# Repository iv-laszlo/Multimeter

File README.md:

# Multimeter

This project is a custom-built Digital Multimeter developed by a student team, as part of an academic project. The device is capable of measuring voltage, current, and resistance, and was designed from the ground up using embedded systems and custom PCB design.

Features

    Measures DC voltage, current, resistance, and temperature

    Built using a microcontroller with analog signal processing

    Designed in KiCad for schematic and PCB layout

    Fully functional firmware written in C/C++

    Simple and intuitive user interface

Tools & Technologies

    Microcontroller: Aruino Nano [ATmega328P]

    KiCad: PCB and schematic design

    C/C++: Firmware development

    Multimeter principles: Analog signal acquisition, ADC, display interface

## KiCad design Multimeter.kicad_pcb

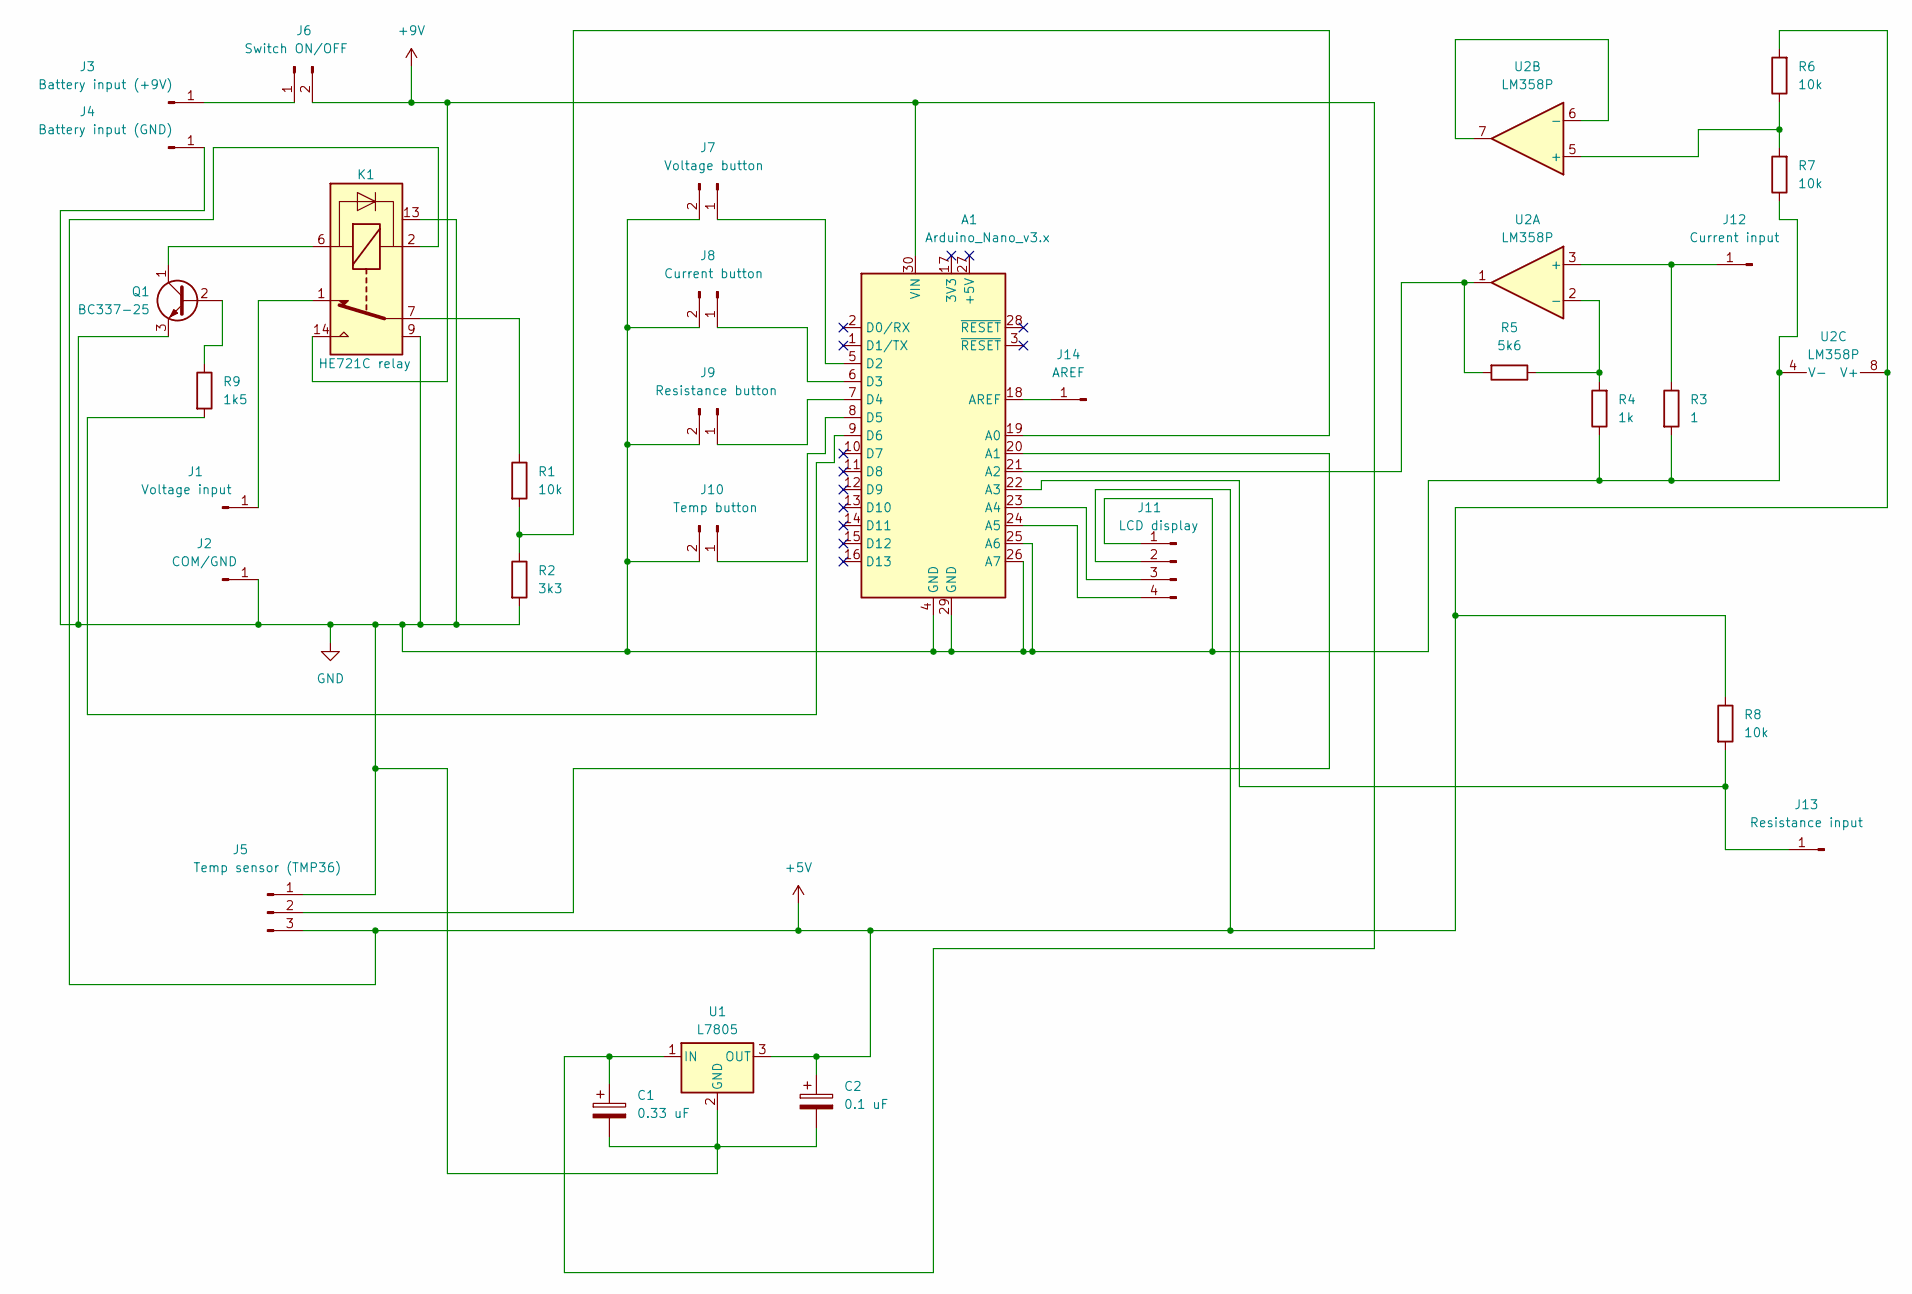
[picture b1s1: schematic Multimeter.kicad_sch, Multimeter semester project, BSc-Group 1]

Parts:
A1: Arduino_Nano_v3.x; Arduino_Nano
C1: 0.33 uF; CP_Radial_Tantal_D4.5mm_P2.50mm
C2: 0.1 uF; CP_Radial_Tantal_D4.5mm_P2.50mm
J1: Voltage input; PinHeader_1x01_P2.54mm_Vertical
J2: COM/GND; PinHeader_1x01_P2.54mm_Vertical
J3: Battery input (+9V); PinHeader_1x01_P2.54mm_Vertical
J4: Battery input (GND); PinHeader_1x01_P2.54mm_Vertical
J5: Temp sensor (TMP36); PinHeader_1x03_P2.54mm_Vertical
J6: Switch ON/OFF; PinHeader_1x02_P2.54mm_Vertical
J7: Voltage button; PinHeader_1x02_P2.54mm_Vertical
J8: Current button; PinHeader_1x02_P2.54mm_Vertical
J9: Resistance button; PinHeader_1x02_P2.54mm_Vertical
J10: Temp button; PinHeader_1x02_P2.54mm_Vertical
J11: LCD display; PinHeader_1x04_P2.54mm_Vertical
J12: Current input; PinHeader_1x01_P2.54mm_Vertical
J13: Resistance input; PinHeader_1x01_P2.54mm_Vertical
J14: AREF; PinHeader_1x01_P2.54mm_Vertical
K1: HE721C relay; HE700
Q1: BC337-25; TO-92_Inline_Wide
R1, R6, R7, R8: 10k; R_Axial_DIN0207_L6.3mm_D2.5mm_P10.16mm_Horizontal
R2: 3k3; R_Axial_DIN0207_L6.3mm_D2.5mm_P10.16mm_Horizontal
R3: 1; R_Axial_DIN0207_L6.3mm_D2.5mm_P10.16mm_Horizontal
R4: 1k; R_Axial_DIN0207_L6.3mm_D2.5mm_P10.16mm_Horizontal
R5: 5k6; R_Axial_DIN0207_L6.3mm_D2.5mm_P10.16mm_Horizontal
R9: 1k5; R_Axial_DIN0207_L6.3mm_D2.5mm_P10.16mm_Horizontal
U1: L7805; TO-220-3_Vertical
U2: LM358P; DIP-8_W7.62mm

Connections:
+5V: C2.1, J5.3, J11.2, K1.2, R6.2, R8.1, U1.3 (OUT), U2.8 (V+)
+9V: A1.30 (VIN), C1.1, J6.2, K1.14, U1.1 (IN)
GND: A1.4 (GND), A1.25 (A6), A1.26 (A7), A1.29 (GND), C1.2, C2.2, J2.1, J4.1, J5.1, J7.2, J8.2, J9.2, J10.2, J11.1, K1.9, K1.13, Q1.3 (E), R2.2, R3.2, R4.1, R7.1, U1.2 (GND), U2.4 (V-)
unnamed: A1.19 (A0), R1.2, R2.1
unnamed: A1.20 (A1), J5.2
unnamed: A1.21 (A2), R5.2, U2.1
unnamed: A1.22 (A3), J13.1, R8.2
unnamed: A1.23 (A4), J11.3
unnamed: A1.24 (A5), J11.4
unnamed: A1.18 (AREF), J14.1
unnamed: A1.5 (D2), J7.1
unnamed: A1.6 (D3), J8.1
unnamed: A1.7 (D4), J9.1
unnamed: A1.8 (D5), J10.1
unnamed: A1.9 (D6), R9.2
unnamed: J1.1, K1.1
unnamed: J3.1, J6.1
unnamed: J12.1, R3.1, U2.3 (+)
unnamed: K1.7, K1.8, R1.1
unnamed: Q1.2 (B), R9.1
unnamed: K1.6, Q1.1 (C)
unnamed: R4.2, R5.1, U2.2 (-)
unnamed: R6.1, R7.2, U2.5 (+)
unnamed: U2.6 (-), U2.7

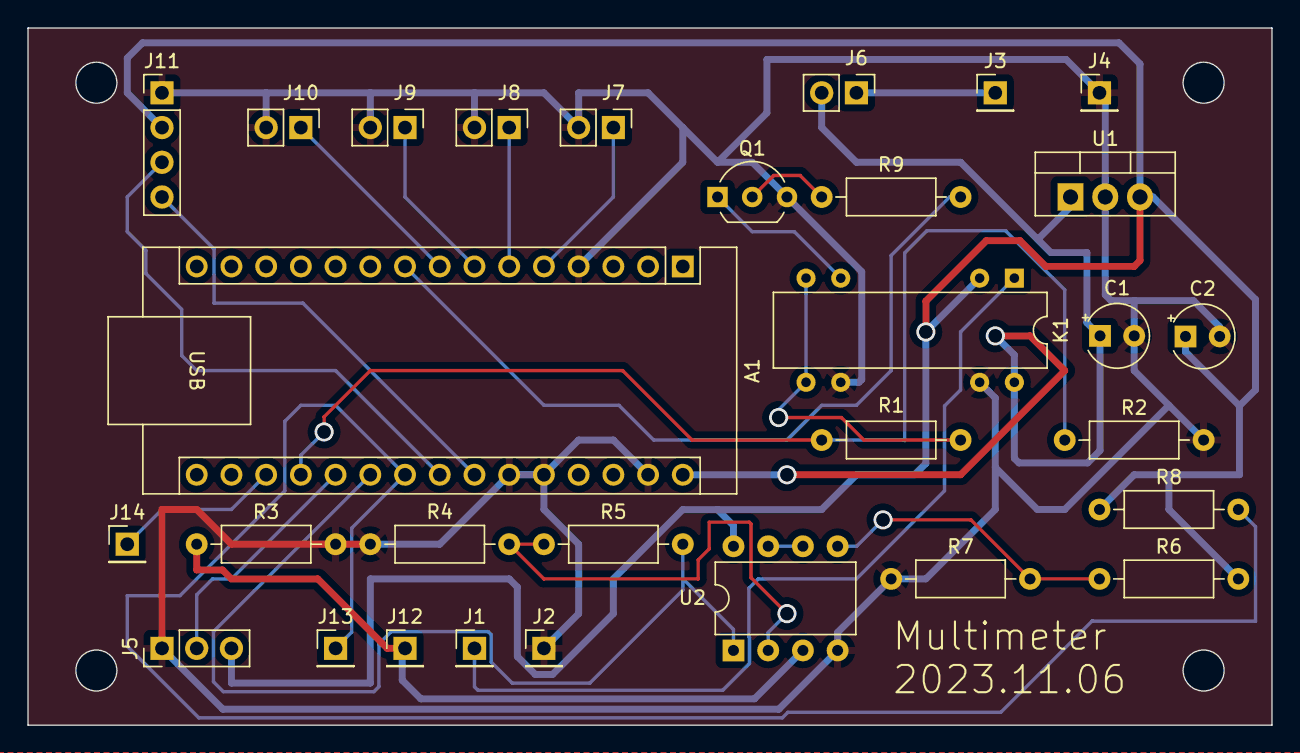
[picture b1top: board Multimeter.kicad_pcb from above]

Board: 2 copper layers, 91.0 x 51.0 mm, 30 parts (0 on the bottom side), 24 nets.

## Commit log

2025-06-28 Create LICENSE
